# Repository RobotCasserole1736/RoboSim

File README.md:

# RoboSim
Arduino-based hardware-in-the-loop simulation of FRC robot hardware.

## Purpose
RoboSim is a set of hardware and software designed to enable simulation of 
mechanical hardware on a robot designed for the First Robotics Competition. 
The goal is to enable mentors and students to design a sufficiently functional plant mode for their robot, 
connect a fully-constructed electrical board with software, and observe the effects of control inputs on 
their simulated robot platform. This allows the electrical, software, and mechanical teams to work more in parallel.

## High level design.
RoboSim is build around an Arduino Mega. There are two sets of peripheral boards which 
expand the arduino's IO capability. The Arduino sends state information to a desktop PC 
running a plant model, and receives return data which it can feed back to the simulated 
robot's electrical board. The plant model on the PC is run using GNU Octave (a free Malab 
alternative). The Octave Plant model simulates the robot hardware (taking only motor and 
solenoid voltages as inputs). Serial data is transfered between the arduino and Octave for 
IO with the electrical board.

## Project Status
RoboSim is currently in development. All releases as of now are tested, but considered "alpha". 

## Screen-shots

## Repository Contents
- arduino_src - source code for the embedded arduino controller inside of RoboSim
- Octave - source code for the Octave-run plant model and GUI
- Eagle - electrical schematics for RoboSim peripheral boards
- PSPICE - electrical simulations for RoboSim peripheral boards
- docs - an increasing collection of documentation.

## Required software:
- Arduino IDE
  - https://www.arduino.cc/en/Main/Software
- Python 3.2 (32bit)- other versions may work but are untested
  - https://www.python.org/download/releases/3.2.5/
- PySerial 2.7 win32 py3k
  -https://pypi.python.org/pypi/pyserial
- GNU Octave + instrument-control package
  - http://www.gnu.org/software/octave/download.html
  - Once installed, run "pkg install -forge instrument-control" at the Octave command window
- Other Tools
  - Eagle PCB design
    - http://www.cadsoftusa.com/download-eagle/
  - LtSpice circuit simulator
    - http://www.linear.com/designtools/software/
  - Autodesk Inventor

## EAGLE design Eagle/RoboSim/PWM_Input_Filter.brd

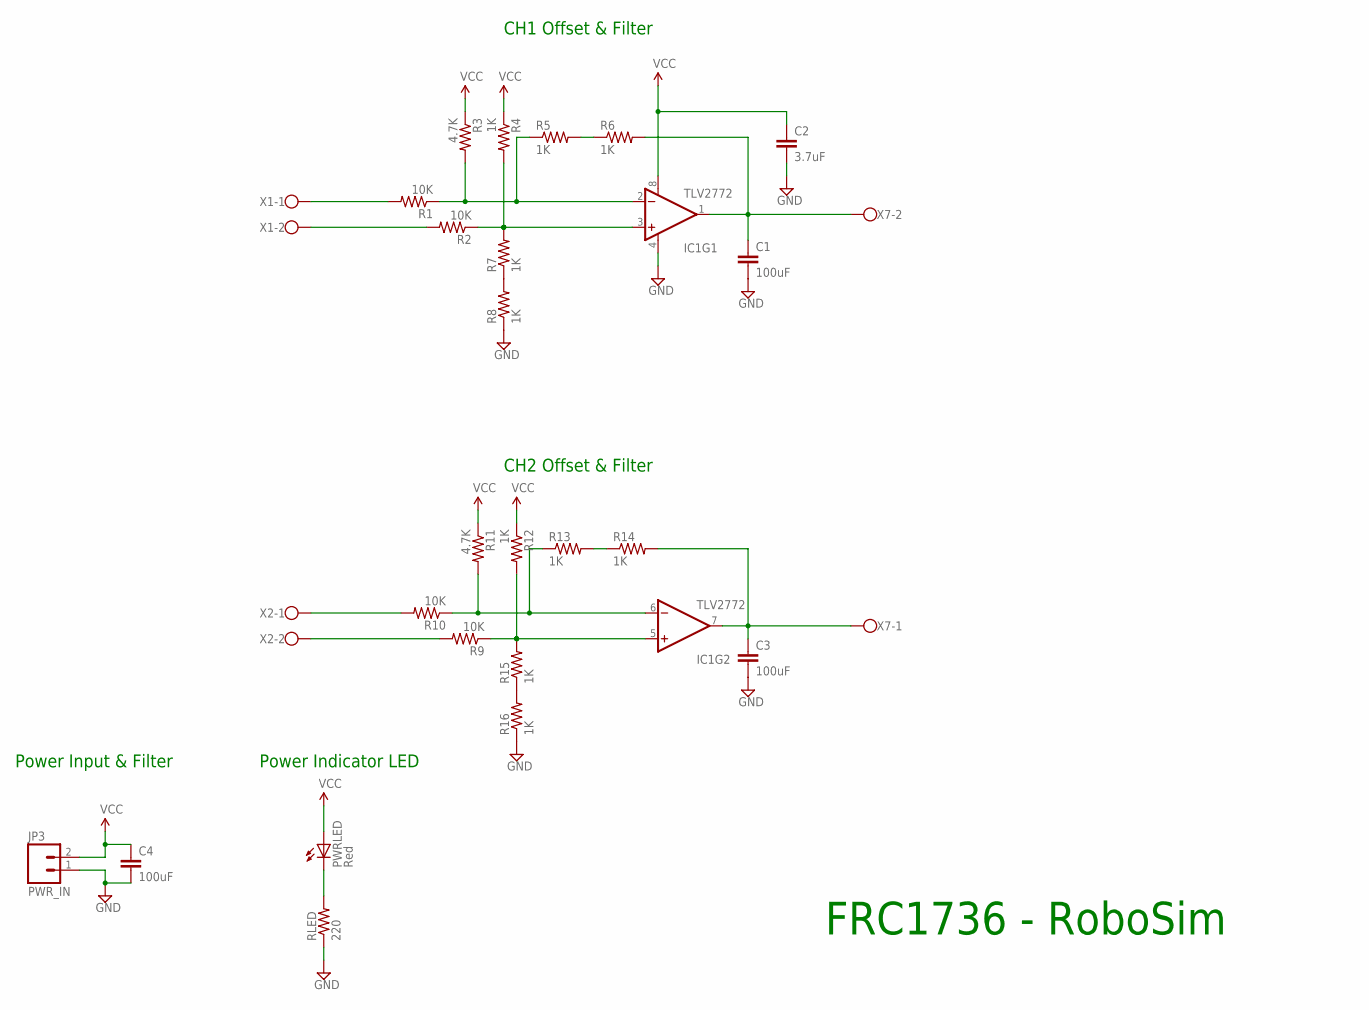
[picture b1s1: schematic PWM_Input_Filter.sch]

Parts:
C1, C3, C4: 100uF; CAP-PTH-SMALL
C2: 3.7uF; CAP-PTH-SMALL
IC1: TLV2772; DIP08
JP3: PWR_IN; 1X02_LOCK
PWRLED: Red; LED5MM
R1, R2, R9, R10: 10K; AXIAL-0.3
R3, R11: 4.7K; AXIAL-0.3
R4, R5, R6, R7, R8, R12, R13, R14, R15, R16: 1K; AXIAL-0.3
RLED: 220; AXIAL-0.3
X1, X2, X7: W237-102

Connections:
GND: C1.2, C2.2, C3.2, C4.2, IC1.4 (V-), JP3.1, R8.P$1 (1), R16.P$1 (1), RLED.P$1 (1)
unnamed: R1.P$2 (2), X1.1
unnamed: R9.P$2 (2), X2.2
unnamed: PWRLED.K (C), RLED.P$2 (2)
unnamed: IC1.2 (-IN), R1.P$1 (1), R3.P$2 (2), R5.P$1 (1)
unnamed: IC1.3 (+IN), R2.P$1 (1), R4.P$2 (2), R7.P$2 (2)
unnamed: R2.P$2 (2), X1.2
unnamed: R5.P$2 (2), R6.P$1 (1)
unnamed: R7.P$1 (1), R8.P$2 (2)
unnamed: IC1.6 (-IN), R10.P$1 (1), R11.P$2 (2), R13.P$1 (1)
unnamed: IC1.5 (+IN), R9.P$1 (1), R12.P$2 (2), R15.P$2 (2)
unnamed: C3.1, IC1.7 (OUT), R14.P$2 (2), X7.1
unnamed: R10.P$2 (2), X2.1
unnamed: R13.P$2 (2), R14.P$1 (1)
unnamed: R15.P$1 (1), R16.P$2 (2)
unnamed: C1.1, IC1.1 (OUT), R6.P$2 (2), X7.2
VCC: C2.1, C4.1, IC1.8 (V+), JP3.2, PWRLED.A, R3.P$1 (1), R4.P$1 (1), R11.P$1 (1), R12.P$1 (1)

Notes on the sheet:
Power Input & Filter
Power Indicator LED
CH1 Offset & Filter
CH2 Offset & Filter
FRC1736 - RoboSim

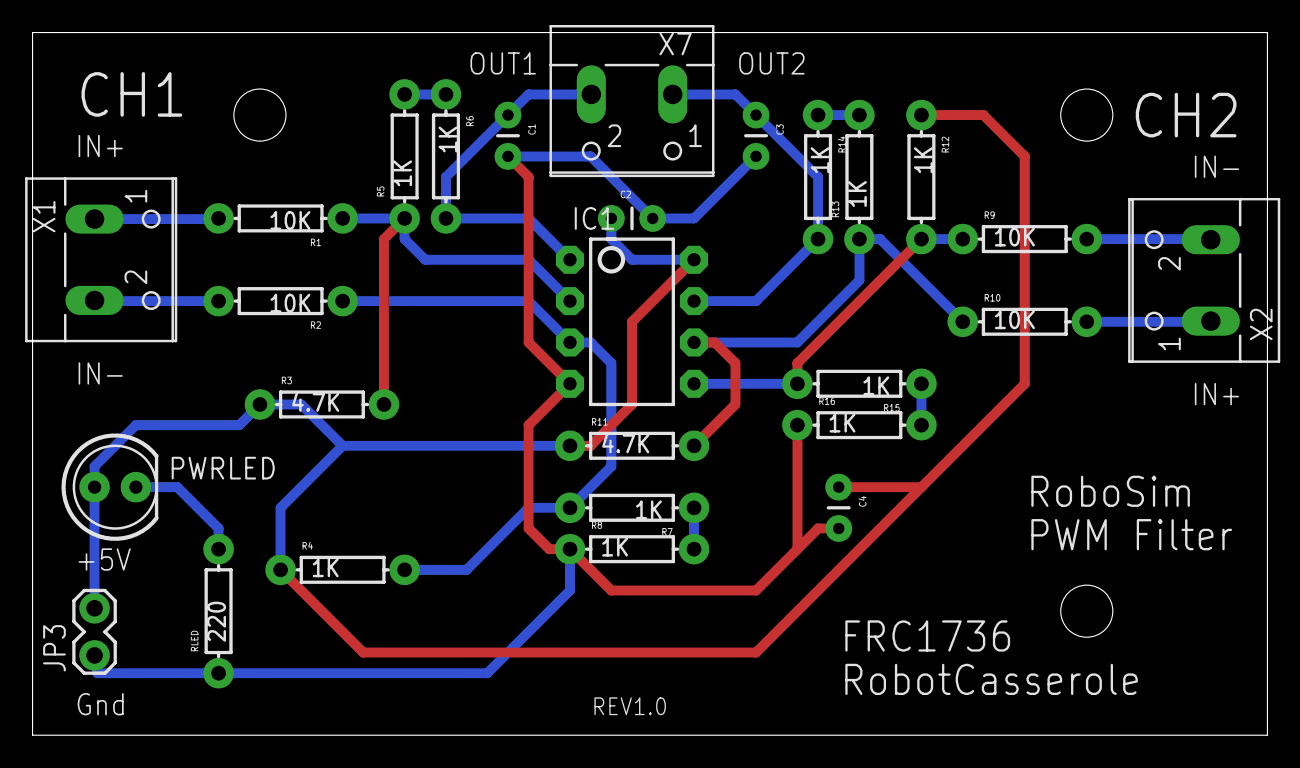
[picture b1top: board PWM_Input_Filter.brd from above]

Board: 2 copper layers, 75.9 x 43.2 mm, 27 parts (0 on the bottom side), 17 nets.

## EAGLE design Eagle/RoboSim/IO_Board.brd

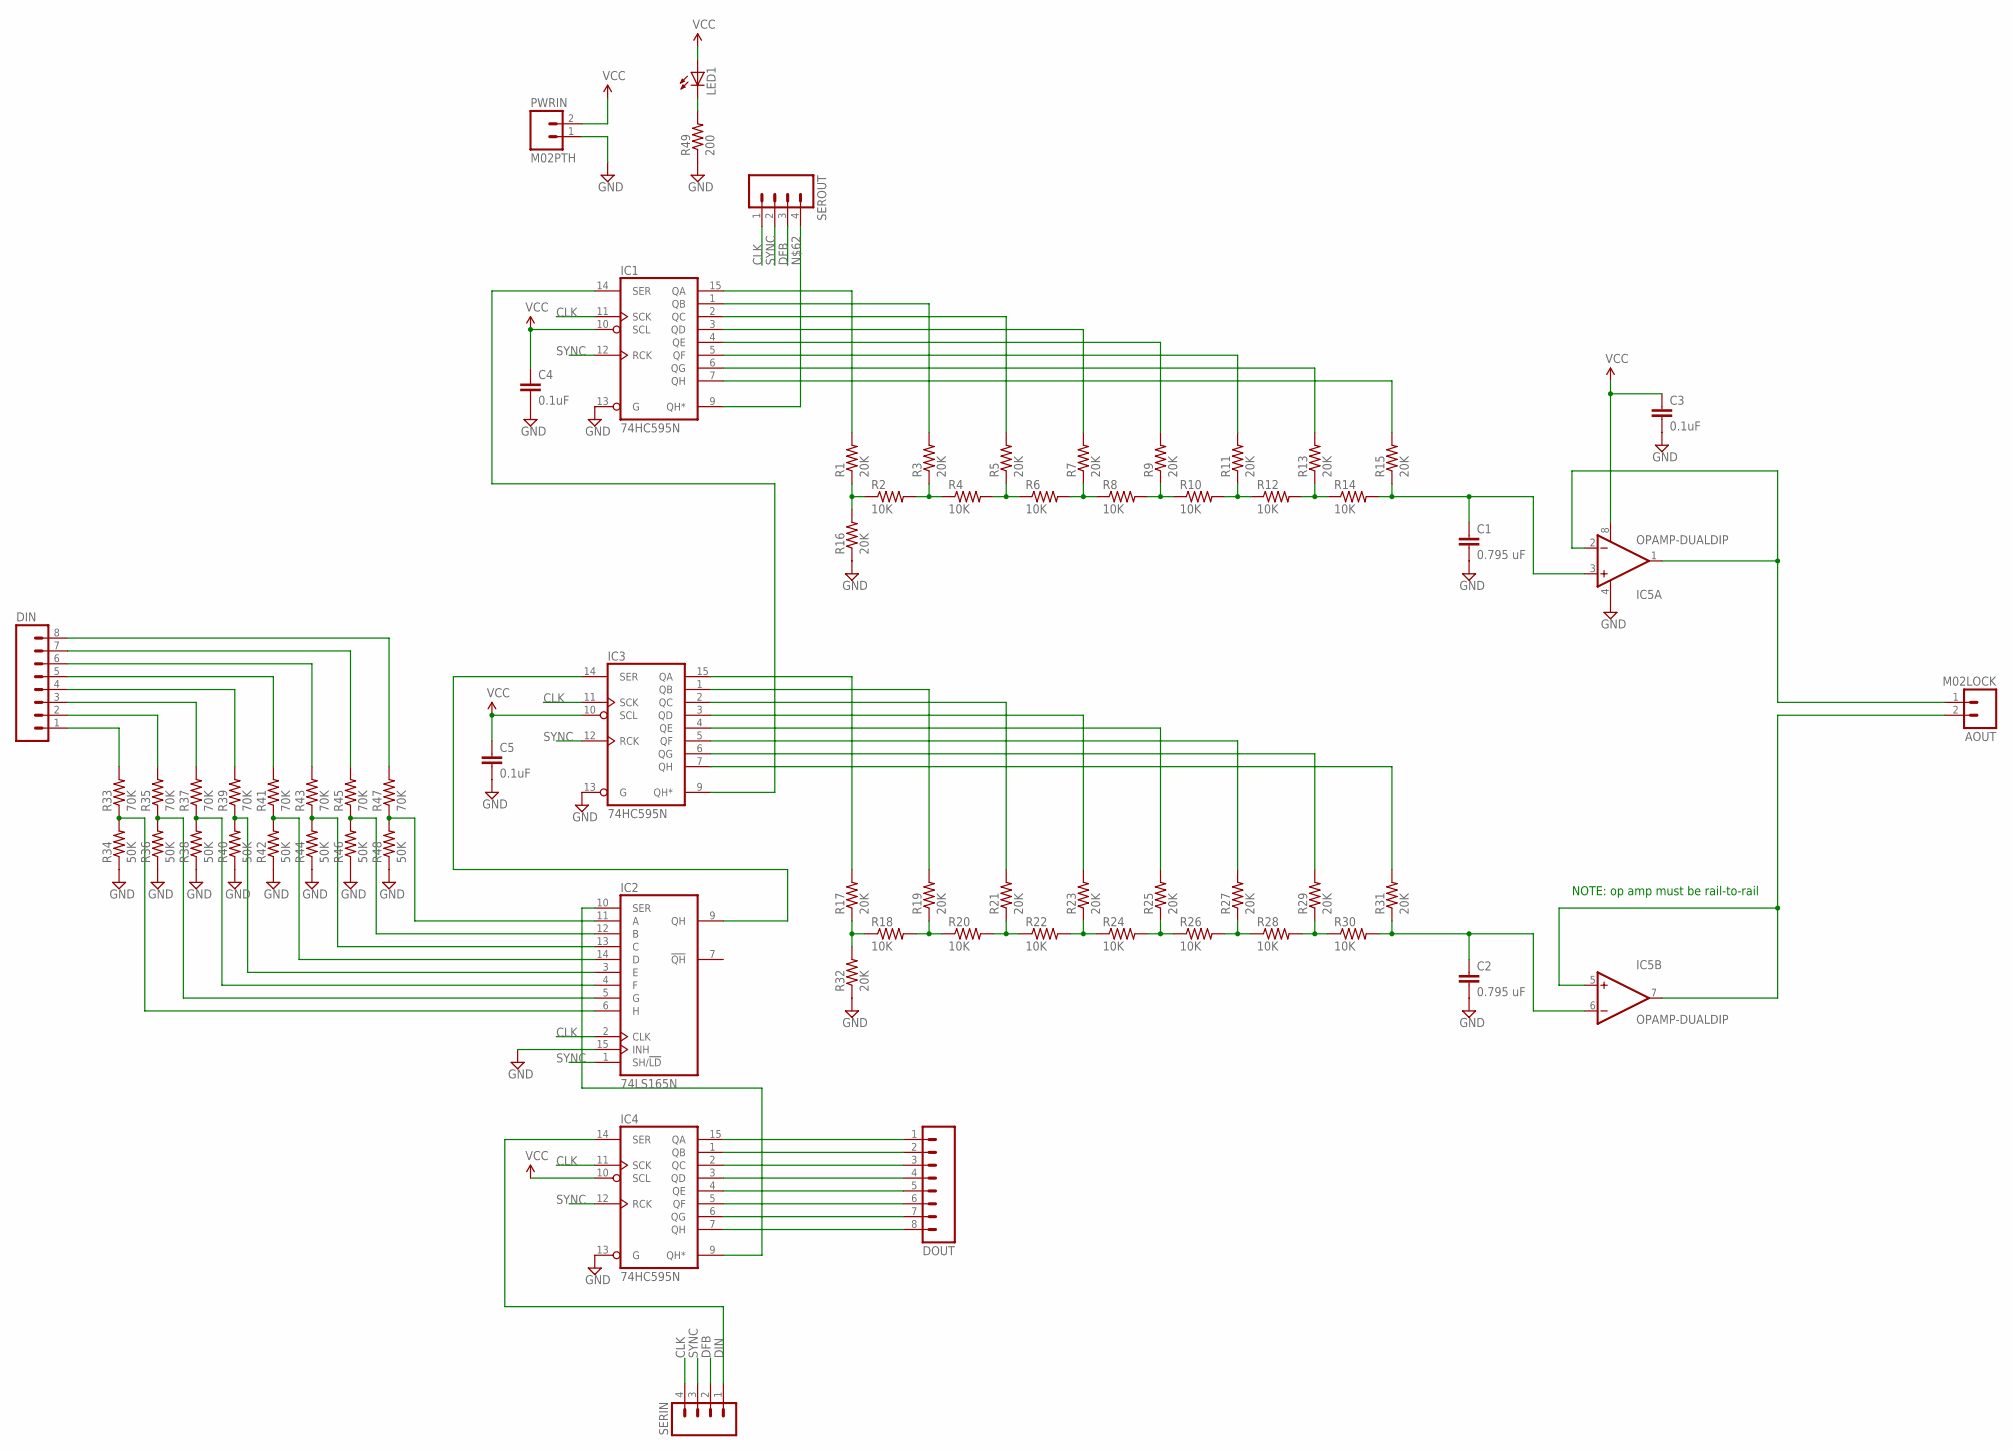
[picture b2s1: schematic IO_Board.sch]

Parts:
AOUT: M02LOCK; 1X02_LOCK
C1, C2: 0.795 uF; CAP-PTH-SMALL
C3, C4, C5: 0.1uF; CAP-PTH-SMALL
DIN: M08LOCK; 1X08_LOCK
DOUT: M08LOCK; 1X08_LOCK
IC1, IC3, IC4: 74HC595N; DIL16
IC2: 74LS165N; DIL16
IC5: OPAMP-DUALDIP; DIP08
LED1: LED5MM
PWRIN: M02PTH; 1X02
R1, R3, R5, R7, R9, R11, R13, R15, R16, R17, R19, R21, R23, R25, R27, R29, R31, R32: 20K; AXIAL-0.1
R2, R4, R6, R8, R10, R12, R14, R18, R20, R22, R24, R26, R28, R30: 10K; AXIAL-0.1
R33, R35, R37, R39, R41, R43, R45, R47: 70K; AXIAL-0.1
R34, R36, R38, R40, R42, R44, R46, R48: 50K; AXIAL-0.1
R49: 200; AXIAL-0.1
SERIN: M04LOCK; 1X04_LOCK
SEROUT: M04LOCK; 1X04_LOCK

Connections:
CLK: IC1.11 (SCK), IC2.2 (CLK), IC3.11 (SCK), IC4.11 (SCK), SERIN.4, SEROUT.1
DFB: SERIN.2, SEROUT.3
DIN: IC4.14 (SER), SERIN.1
GND: C1.2, C2.2, C3.2, C4.2, C5.2, IC1.8 (GND), IC1.13 (G), IC2.8 (GND), IC2.15 (INH), IC3.8 (GND), IC3.13 (G), IC4.8 (GND), IC4.13 (G), IC5.4 (V-), PWRIN.1, R16.P$1 (1), R32.P$1 (1), R34.P$1 (1), R36.P$1 (1), R38.P$1 (1), R40.P$1 (1), R42.P$1 (1), R44.P$1 (1), R46.P$1 (1), R48.P$1 (1), R49.P$1 (1)
unnamed: IC1.7 (QH), R15.P$2 (2)
unnamed: AOUT.2, IC5.5 (+IN), IC5.7 (OUT)
unnamed: IC1.6 (QG), R13.P$2 (2)
unnamed: IC1.5 (QF), R11.P$2 (2)
unnamed: IC1.4 (QE), R9.P$2 (2)
unnamed: IC1.3 (QD), R7.P$2 (2)
unnamed: IC1.2 (QC), R5.P$2 (2)
unnamed: IC1.1 (QB), R3.P$2 (2)
unnamed: IC1.15 (QA), R1.P$2 (2)
unnamed: R1.P$1 (1), R2.P$1 (1), R16.P$2 (2)
unnamed: R2.P$2 (2), R3.P$1 (1), R4.P$1 (1)
unnamed: R4.P$2 (2), R5.P$1 (1), R6.P$1 (1)
unnamed: R6.P$2 (2), R7.P$1 (1), R8.P$1 (1)
unnamed: R8.P$2 (2), R9.P$1 (1), R10.P$1 (1)
unnamed: R10.P$2 (2), R11.P$1 (1), R12.P$1 (1)
unnamed: R12.P$2 (2), R13.P$1 (1), R14.P$1 (1)
unnamed: C1.1, IC5.3 (+IN), R14.P$2 (2), R15.P$1 (1)
unnamed: AOUT.1, IC5.1 (OUT), IC5.2 (-IN)
unnamed: IC3.7 (QH), R31.P$2 (2)
unnamed: IC3.6 (QG), R29.P$2 (2)
unnamed: IC3.5 (QF), R27.P$2 (2)
unnamed: IC3.4 (QE), R25.P$2 (2)
unnamed: IC3.3 (QD), R23.P$2 (2)
unnamed: IC3.2 (QC), R21.P$2 (2)
unnamed: IC3.1 (QB), R19.P$2 (2)
unnamed: IC3.15 (QA), R17.P$2 (2)
unnamed: R17.P$1 (1), R18.P$1 (1), R32.P$2 (2)
unnamed: R18.P$2 (2), R19.P$1 (1), R20.P$1 (1)
unnamed: R20.P$2 (2), R21.P$1 (1), R22.P$1 (1)
unnamed: R22.P$2 (2), R23.P$1 (1), R24.P$1 (1)
unnamed: R24.P$2 (2), R25.P$1 (1), R26.P$1 (1)
unnamed: R26.P$2 (2), R27.P$1 (1), R28.P$1 (1)
unnamed: R28.P$2 (2), R29.P$1 (1), R30.P$1 (1)
unnamed: C2.1, IC5.6 (-IN), R30.P$2 (2), R31.P$1 (1)
unnamed: IC2.6 (H), R33.P$1 (1), R34.P$2 (2)
unnamed: IC2.5 (G), R35.P$1 (1), R36.P$2 (2)
unnamed: IC2.4 (F), R37.P$1 (1), R38.P$2 (2)
unnamed: IC2.3 (E), R39.P$1 (1), R40.P$2 (2)
unnamed: IC2.14 (D), R41.P$1 (1), R42.P$2 (2)
unnamed: IC2.13 (C), R43.P$1 (1), R44.P$2 (2)
unnamed: IC2.12 (B), R45.P$1 (1), R46.P$2 (2)
unnamed: IC2.11 (A), R47.P$1 (1), R48.P$2 (2)
unnamed: DOUT.1, IC4.15 (QA)
unnamed: DOUT.2, IC4.1 (QB)
unnamed: DOUT.3, IC4.2 (QC)
unnamed: DOUT.4, IC4.3 (QD)
unnamed: DOUT.5, IC4.4 (QE)
unnamed: DOUT.6, IC4.5 (QF)
unnamed: DOUT.7, IC4.6 (QG)
unnamed: DOUT.8, IC4.7 (QH)
unnamed: DIN.8, R47.P$2 (2)
unnamed: DIN.7, R45.P$2 (2)
unnamed: DIN.6, R43.P$2 (2)
unnamed: DIN.5, R41.P$2 (2)
unnamed: DIN.4, R39.P$2 (2)
unnamed: DIN.3, R37.P$2 (2)
unnamed: DIN.2, R35.P$2 (2)
unnamed: DIN.1, R33.P$2 (2)
unnamed: IC2.9 (QH), IC3.14 (SER)
unnamed: LED1.K (C), R49.P$2 (2)
unnamed: IC1.9 (QH*), SEROUT.4
unnamed: IC1.14 (SER), IC3.9 (QH*)
SYNC: IC1.12 (RCK), IC2.1 (SH/!LD), IC3.12 (RCK), IC4.12 (RCK), SERIN.3, SEROUT.2
VCC: C3.1, C4.1, C5.1, IC1.10 (SCL), IC1.16 (VCC), IC2.16 (VCC), IC3.10 (SCL), IC3.16 (VCC), IC4.10 (SCL), IC4.16 (VCC), IC5.8 (V+), LED1.A, PWRIN.2

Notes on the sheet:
NOTE: op amp must be rail-to-rail

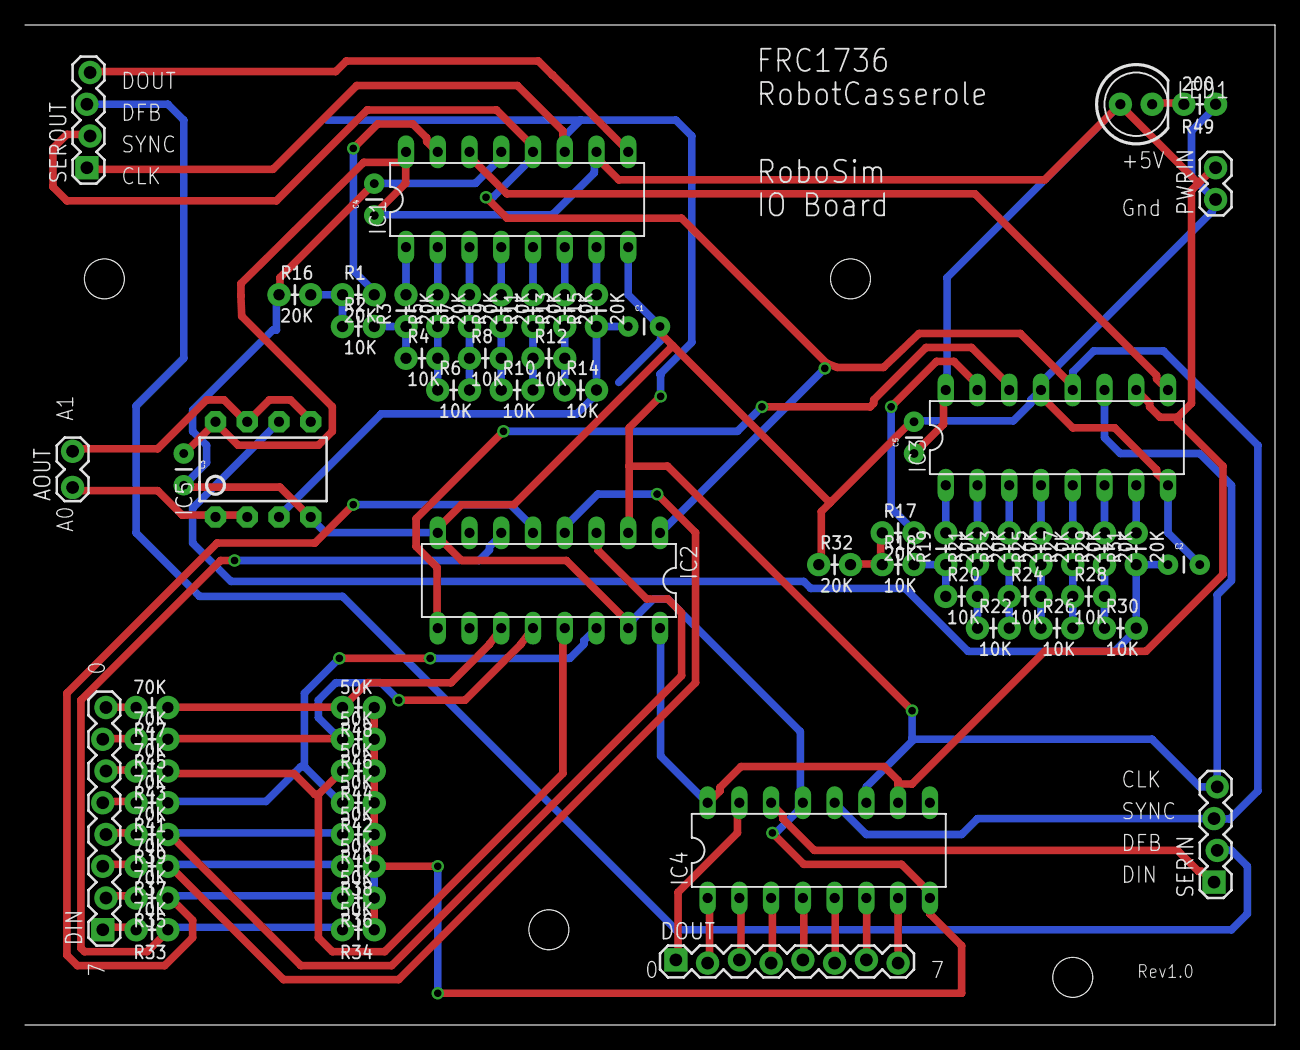
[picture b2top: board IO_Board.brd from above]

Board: 2 copper layers, 100.0 x 80.0 mm, 66 parts (0 on the bottom side), 68 nets.

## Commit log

2015-03-24 initial content commit. Basic structure laid out, quadrature encoder emulation started
2015-03-24 work in progrss - encoder emulators generate output, but scaling is not yet correct
2015-03-26 Updated scaling logic, but untested
2015-03-26 confirmed timing logic, added main loop with 0.1s Ts, started analog reads for motors
2015-03-28 added input PWM filter pspice simulation, schematic, and board files
2015-03-28 added hw led flash and analog reads and plant skeleton function
2015-03-28 updated line endings
2015-03-29 Added IO board schematic and board
2015-04-03 started sw for io card
2015-04-03 continued development on io card interface
2015-04-03 finished writieng code for IO board. need to validate code and add more comments
2015-04-12 commit misc. changes from save
2015-04-12 started python gui
2015-04-17 updated gui code, basic animation possible with robot.
2015-05-01 updated op amp part number
2015-05-02 added results file and pspice decided it needed to create new files.
2015-05-21 Corrected sync signal behavor, still need to test on board
2015-05-21 Temp - added debugging changes
2015-05-22 continued debugging IO board
2015-05-22 Further debugging
2015-05-23 Finished debugging - io card serial transfer functions are fully functional
2015-05-29 updated wiring diagram for DAC's. added fast io functions to arduino code. Added test vector generation. Still tuning good compromise between signal fedility and processor load
2015-05-29 forgot to add eagle project
2015-06-11 Fixed issue with ch1 analog voltage follower. confirmed full board functionality
2015-06-25 added PWM input filter V2
2015-06-26 actually fixed input circuit
2015-07-02 Updated pwm input filter schematic
2015-07-08 Added get_motor_in_voltage_map() to use a configurable map for each ADC input to translate into a motor voltage.
2015-07-10 Added matlab simulation of motor model
2015-07-13 updated motor model with actual numbers. Isn't 100% accurate, especially with steady-state speed under no load...
2015-07-14 Tweaked inductance val and friction vals, much more realistic looking model
2015-07-14 updated comments and title quotations for matlab compatibility.
2015-07-15 added test of octave's animation abilities. Basic field plus robot moving in circle
2015-07-15 Changed folder names since we're using Octave instead of matlab
2015-07-15 added serial test (not tested yet) and cleaned up animation test
2015-07-17 completed searial test. works freakin awesome
2015-07-17 Updated readmes, removed GUI/ since it's no longer needed
2015-07-17 added docs, new plant model, gitignore
2015-07-17 made the gitignore actually work
2015-07-17 fixed file names to not be silly. SCREAMING_SNAKE_CASE is for silly developers.
2015-07-17 added comments to plant file. still need to implement out the wazoo.
2015-07-20 Work-in-progress on setting up octave plant model to work with arduino. Need to still adjust quad encoder setup to read period commands (in ms) from PC, and actually write serial packet send/recieve 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
2015-07-20 fixed gitignore to not archive octave workspace files
2015-07-20 added serial tx/rx functions to arduino code, fleshed out definition of packet in octave plant comments. Still untested, though.
2015-07-20 added serial data packet send/recieve functions to roboSim arduino
2015-07-21 cleaned up plant model, started gui test of robosim hardware
2015-07-21 gui WIP
2015-07-21 more gui WIP. need to add inputs and serial read/write code
2015-07-22 io board started acting up, debugging wip
2015-07-22 added gui inputs for encoder outputs. Tested serial send loop
2015-07-22 continued gui work. still need to put together packet assembly and read code, and GUI outputs for recieved packets
2015-07-25 started moving serial functions to common file, cleaned up gui comments
2015-07-25 test gui serial debugged and outputs user interface functional-ish. Need to continue cleaning up timing operations
2015-07-26 Fixed up delay timing logic. GUI is functional, although do not have all display outputs there yet
2015-07-26 confirmed test app is working, and serial protocol works as advertized
2015-07-28 Got rtos pretty much working. Need to tweak stack size parameters and add comments so I remember what the heck I did this late on a work night
2015-08-01 updated test gui octave script and eagle file format, as well as readme with install instructions
2015-08-04 removed _backup file
2015-08-05 Updated to print malloc usage optionally, reduced idle task function call depth
2015-08-05 reduced stack sizes and number of possible priorities
2015-08-18 updated test gui to run from B or C drives
2015-08-19 debugged serial detection, added test script, and added to main test gui
2015-08-19 cleaned up exit code
2015-08-19 Reduced digital pulse time and added interrupt disable around each io card byte transmit. Haven't verified this didnt' break anything yet, although it looks good for now.
2015-08-20 Initial Model Changes after Chris's really initial model
2015-08-21 updated circuit 1 on the board to proper experimented values. Need to update the others as well
2015-08-21 updated resistor values and op-amp configuration
2015-08-22 changed pins to screw terminals and made resistors surface mount. Still need to position components and route
2015-08-22 added new gitignore for eagle
2015-08-22 Enforced new gitignore for eagle
2015-08-22 trimmed pwm filter circuit schematic to just show two channels, fixed up schematic
2015-08-22 added extra text to schematic
2015-08-22 moved pwm filter's brd annotation layers again so they'd show up on the board silkscreen
2015-08-22 updated io board schematic, both PCB's ready for production
2015-08-25 Added enclosure
2015-08-25 started making panel parts from enclosure
2015-08-26 Finished parted-out enclosure CAD, added mounting holes and chef hat to pcb's
2015-08-28 cleaned up Eagle folder, corrected CH2 label (wrong layer)
2015-08-28 Debugging robosim test gui. Timing was off which was creating lag in the test gui. However, now packet reciving is unstable
2015-08-28 Quick side test, may not actually use...
2015-08-28 updated gui to display outputs. Inputs are still not reading fast enough though, serial rx buffer is filling too fast
2015-08-28 added inputs from robosim to test gui, tweaking timing. fixed lag, but get missed packets every now and then
2015-08-29 Fixed the serial read/write functionality to add checksum checker, and get around odd multi-byte read bug. Test gui seems to work perfectly now. Ran for like 20 minutes and no bad serial reads
2015-09-04 added compressor&tank model. Needs to be tested still
2015-09-05 added test for compressor&tank model. Tweaked values per Andymark's website. Their website still claims it can fill a 500mL tank to 120PSI in 13 seconds, but my model is taking closer to two minutes.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
2015-09-05 much more realistic since we have the right sized tanks now
2015-09-06 added pressure sensor model and simple pneumatic system test. Still need to tune cylinder values for realistic behavior.
2015-10-04 Updated required sw install
2015-10-04 Copied arduino src and started working for arduino Mega. Added OLED display routines. Increasesd memory allocaions and added OS error print-to-OLED display handling
2015-10-04 Added memory usage tracking fcn. DOesn't look like it actually works. Perhaps we need to look at the RTOS...
2015-10-04 restructured arduino RTOS mega folder into actual folders, added python build utility
2015-10-04 added arduino exe and serial port autodetect to build script
2015-10-05 removed old codebases
2015-10-05 eliminated interrupt disable around io board read/write to increase accuracy of encoders. took extra debug info out of build.py. added encoder period screens to display
2015-10-06 added useless screensaver, cranked up the loop rate of the screen refresh to make things smoother. Maybe it still works?
2015-10-06 added optional robosim HW interaction to main sim model
2015-10-13 renamed main roboSim folder to main
2015-10-13 added 5 point map and integrated for analog reads. Need to test and tune.
2015-10-14 updated boards 1 and 2 cal values
2015-10-15 finished updates to cal values for motor inputs
2015-10-17 added top-level schematic. Adjusted output pin numbers
2015-10-28 reworked part of plant model to work. Robot can now move in one dimension
2015-10-28 added y force, doesn't do anything yet.
2015-10-28 added robot draw and field collision detection in 1D. Framework set for rotation calculations
2015-10-29 Getting closer... rotation and friction added. Still some odd behavior with motor speeds...
2015-10-30 Made some more tweaks to the plant model, still not 100% working
2015-10-31 Fixed math error in robot motor speed calculation
    Added "Config Calc" structure for robot to minimize re-calculation of constants every loop
    cleaned up some formatting
    adjusted robot and field physical params to match 2015 game closer.
2015-10-31 Added battery charge electrical model
    Pulled CIM motor model from common lib area
    Removed cloned CIM motor model
    Minor comment udpates
2015-10-31 Updated motor input voltages to be scaled by system voltage
    Minor testcase cleanup
2015-10-31 Added build options to python Arduino build script
    more robust board type detection
2015-11-01 Moved motor sim model back to standard lib/lib_test folders
2015-11-01 Fixed motor model. Confirmed current draw looks reasonable.
2015-11-05 Updated sample time to attempt a 50ms sample time. not sure if it works or not. maybe can go slower, maybe need faster?
2015-11-06 added some starts to the docs, still working on sample time
2015-11-11 removed lyx temp file. Corrected 5 pt map bug. Updated sample time to be 50ms. Some occasional missed sample points, but nothing major
2015-11-12 Initial commit of main breaker implementation
2015-11-14 Aded drawing for sim robot
2015-11-14 Re-organized docs folder
2015-11-14 Finished academic primer for RoboSim
2015-11-14 added friction to academic background, along with some illustrations
2015-11-14 updated analysis pdf and cleaned up code comments and format for arduino rtos. Need to test build.
2015-11-15 Fixed missing header in hwconfig.h, updated make utility to print a help message
2015-11-15 added doc on motor model derivation
2015-11-18 added start to drivetrain integrated model description. Still need electrical and pneumatic and field interactions
2015-11-19 added electrical subsystem description, cleaned up a bit of the software. Started describing software architecture
2015-11-25 continued updates on robot analysis doc
2015-11-26 Added compressor model to sim
2015-11-27 Added licences for everything I could find. This will have to be a work in progress to keep all the open-source licenses up to date. Additionally we shoudl probably start to develop our own license f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
2015-11-27 Added screnshots
2015-12-07 More updates to documentation, and made the field drawing look prettier. Removed some unused files and updated some sscreenshots.
2015-12-07 removed merge files
2016-01-06 Quick testing and updated readme
2016-01-06 More sim testcase updates, added gif
2016-01-06 fixed readme issue
2016-12-03 Added model params for andymark 1.1 compressor, and a test to delta the behavior against the old vaiar 090 one. Data still shows both compressors easily outperforming the quoted values on andymark...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

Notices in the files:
parts and their libraries:
SparkFun-Connectors: Licensing: CC v3.0 Share-Alike You are welcome to use this library for commercial purposes.
